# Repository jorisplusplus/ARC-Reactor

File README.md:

# ARC-Reactor
Based on https://www.thingiverse.com/thing:2799642
This pcb fits inside the center and has 25 ws2812b leds.

#### Necessary parts
- 10x 10uF 0805 capacitors
- 2x 10K 0805 resistors
- 1x NCP1117 3.3V regulator
- 25x WS2812b leds
- 1x ESP-03
- 1x 92mm RGB led ring [(example)](https://nl.aliexpress.com/item/24-LEDs-WS2812B-WS2812-5050-RGB-LED-Pixel-Ring-LED-Lamp-Ring-Licht-Individueel-Adresseerbare-Volledige/32851871739.html?spm=a2g0z.search0104.3.148.d8b5258a7AJyhS&ws_ab_test=searchweb0_0%2Csearchweb201602_2_10152_10151_10065_10344_10068_10342_10343_10340_10341_10696_10084_10083_10618_10304_10307_10301_5711220_10313_10059_10534_100031_10103_10624_10623_443_10622_10621_10620%2Csearchweb201603_49%2CppcSwitch_7&algo_expid=6a1f9e89-2191-4e61-bda5-65054549bfd7-22&algo_pvid=6a1f9e89-2191-4e61-bda5-65054549bfd7&priceBeautifyAB=0)

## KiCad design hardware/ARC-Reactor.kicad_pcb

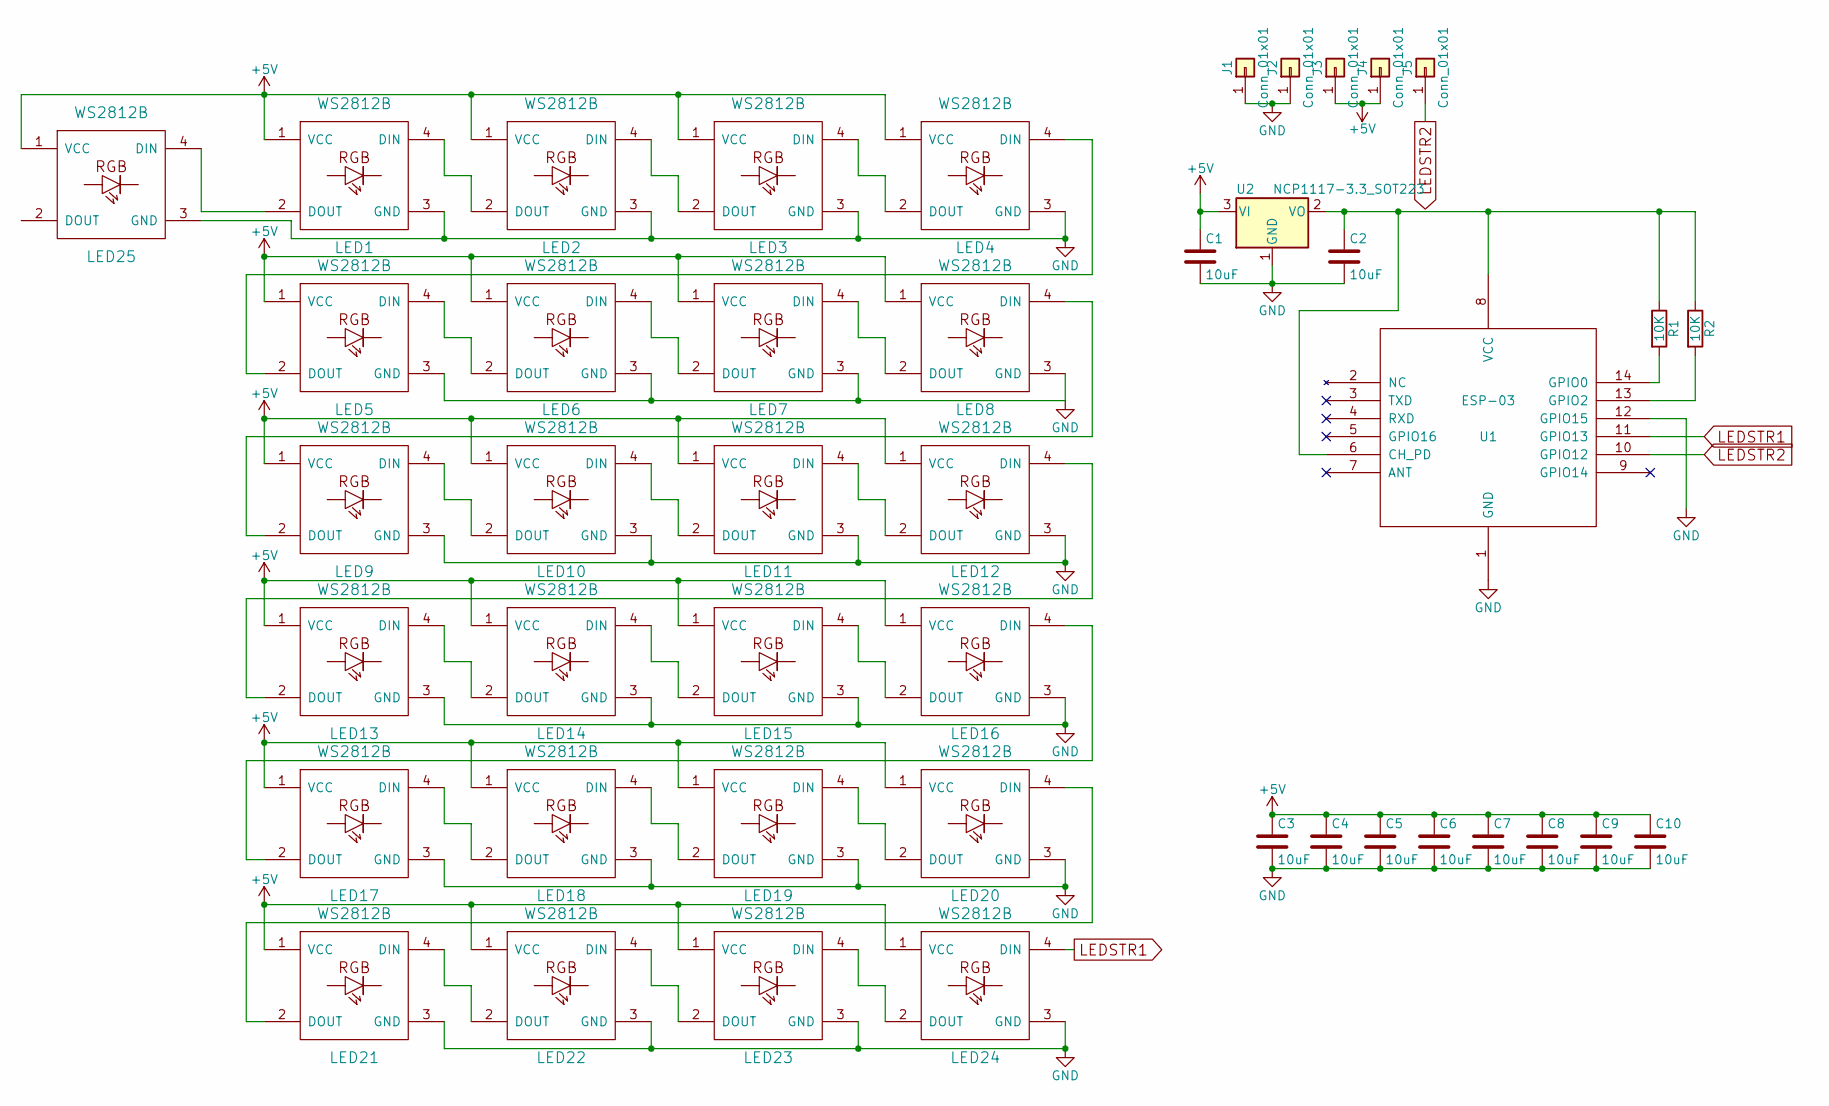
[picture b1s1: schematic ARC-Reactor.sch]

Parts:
C1, C2, C3, C4, C5, C6, C7, C8, C9, C10: 10uF; C_0805
J1, J2, J3, J4, J5: Conn_01x01; 1Pin
LED1, LED2, LED3, LED4, LED5, LED6, LED7, LED8, LED9, LED10, LED11, LED12, LED13, LED14, LED15, LED16, LED17, LED18, LED19, LED20, LED21, LED22, LED23, LED24, LED25: WS2812B
R1, R2: 10K; R_0805
U1: ESP-03
U2: NCP1117-3.3_SOT223; SOT-223-3Lead_TabPin2

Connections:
+5V: C1.1, C3.1, C4.1, C5.1, C6.1, C7.1, C8.1, C9.1, C10.1, J3.1, J4.1, LED1.1 (VCC), LED2.1 (VCC), LED3.1 (VCC), LED4.1 (VCC), LED5.1 (VCC), LED6.1 (VCC), LED7.1 (VCC), LED8.1 (VCC), LED9.1 (VCC), LED10.1 (VCC), LED11.1 (VCC), LED12.1 (VCC), LED13.1 (VCC), LED14.1 (VCC), LED15.1 (VCC), LED16.1 (VCC), LED17.1 (VCC), LED18.1 (VCC), LED19.1 (VCC), LED20.1 (VCC), LED21.1 (VCC), LED22.1 (VCC), LED23.1 (VCC), LED24.1 (VCC), LED25.1 (VCC), U2.3 (VI)
GND: C1.2, C2.2, C3.2, C4.2, C5.2, C6.2, C7.2, C8.2, C9.2, C10.2, J1.1, J2.1, LED1.3 (GND), LED2.3 (GND), LED3.3 (GND), LED4.3 (GND), LED5.3 (GND), LED6.3 (GND), LED7.3 (GND), LED8.3 (GND), LED9.3 (GND), LED10.3 (GND), LED11.3 (GND), LED12.3 (GND), LED13.3 (GND), LED14.3 (GND), LED15.3 (GND), LED16.3 (GND), LED17.3 (GND), LED18.3 (GND), LED19.3 (GND), LED20.3 (GND), LED21.3 (GND), LED22.3 (GND), LED23.3 (GND), LED24.3 (GND), LED25.3 (GND), U1.1 (GND), U1.12 (GPIO15), U2.1 (GND)
LEDSTR1: LED24.4 (DIN), U1.11 (GPIO13)
LEDSTR2: J5.1, U1.10 (GPIO12)
unnamed: C2.1, R1.1, R2.1, U1.6 (CH_PD), U1.8 (VCC), U2.2 (VO)
unnamed: LED1.2 (DOUT), LED25.4 (DIN)
unnamed: LED1.4 (DIN), LED2.2 (DOUT)
unnamed: LED2.4 (DIN), LED3.2 (DOUT)
unnamed: LED3.4 (DIN), LED4.2 (DOUT)
unnamed: LED4.4 (DIN), LED5.2 (DOUT)
unnamed: LED5.4 (DIN), LED6.2 (DOUT)
unnamed: LED6.4 (DIN), LED7.2 (DOUT)
unnamed: LED7.4 (DIN), LED8.2 (DOUT)
unnamed: LED8.4 (DIN), LED9.2 (DOUT)
unnamed: LED9.4 (DIN), LED10.2 (DOUT)
unnamed: LED10.4 (DIN), LED11.2 (DOUT)
unnamed: LED11.4 (DIN), LED12.2 (DOUT)
unnamed: LED12.4 (DIN), LED13.2 (DOUT)
unnamed: LED13.4 (DIN), LED14.2 (DOUT)
unnamed: LED14.4 (DIN), LED15.2 (DOUT)
unnamed: LED15.4 (DIN), LED16.2 (DOUT)
unnamed: LED16.4 (DIN), LED17.2 (DOUT)
unnamed: LED17.4 (DIN), LED18.2 (DOUT)
unnamed: LED18.4 (DIN), LED19.2 (DOUT)
unnamed: LED19.4 (DIN), LED20.2 (DOUT)
unnamed: LED20.4 (DIN), LED21.2 (DOUT)
unnamed: LED21.4 (DIN), LED22.2 (DOUT)
unnamed: LED22.4 (DIN), LED23.2 (DOUT)
unnamed: LED23.4 (DIN), LED24.2 (DOUT)
unnamed: R1.2, U1.14 (GPIO0)
unnamed: R2.2, U1.13 (GPIO2)

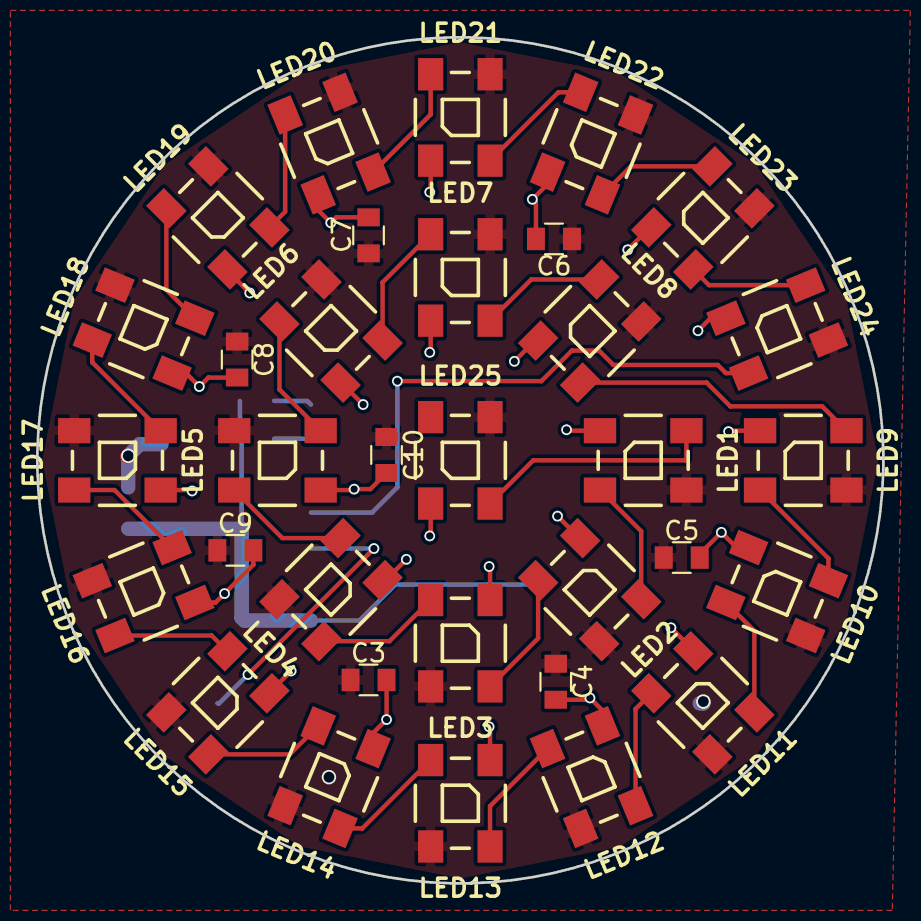
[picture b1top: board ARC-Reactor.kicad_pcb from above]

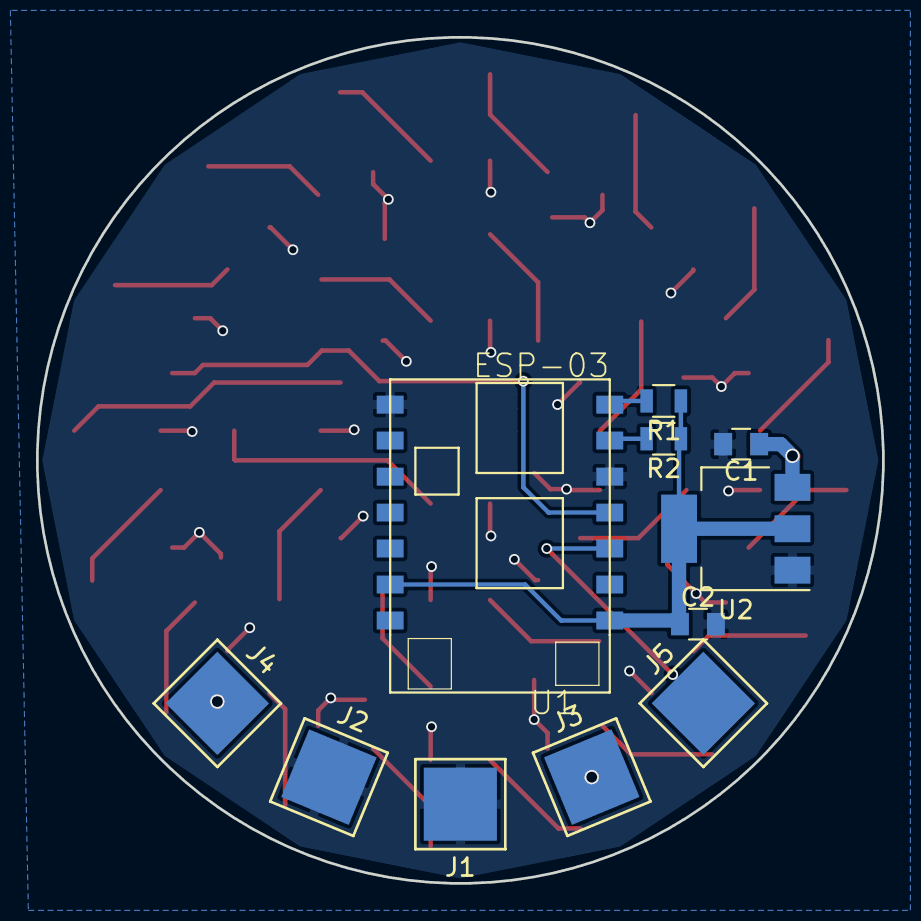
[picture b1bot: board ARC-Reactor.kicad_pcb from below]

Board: 2 copper layers, 47.0 x 47.0 mm, 44 parts (11 on the bottom side), 31 nets.

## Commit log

2018-03-26 Added necessary parts
2018-03-30 Added modified stl
